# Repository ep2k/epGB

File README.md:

# epGB - Game Boy / Game Boy Color Emulator on an FPGA

epGB is an implementation of Nintendo's __Game Boy__ (__GB__) and __Game Boy Color__ (__GBC__) written in SystemVerilog.
It works on an FPGA board with a board for connection to GB/GBC cartridges.

It has no built-in MBCs, and can basically only operate in real-time communication with cartridges.

The system automatically detects whether the cartridge is "for GB", "GB/GBC dual compatible" or "for GBC only" and starts up in GB mode or GBC mode accordingly.
In the case of a "GB/GBC dual compatible" cartridge, it is also possible to force startup in GB mode.

By using an expansion board equipped with a link port, it is possible to communicate with an actual GB/GBC device via a Nintendo __Game Link Cable__.

The operation has been confirmed with Terasic DE0-CV Board.

---
Demo Video:  
<https://youtu.be/pQHvBj9nH0k>

---

<br>

")

")

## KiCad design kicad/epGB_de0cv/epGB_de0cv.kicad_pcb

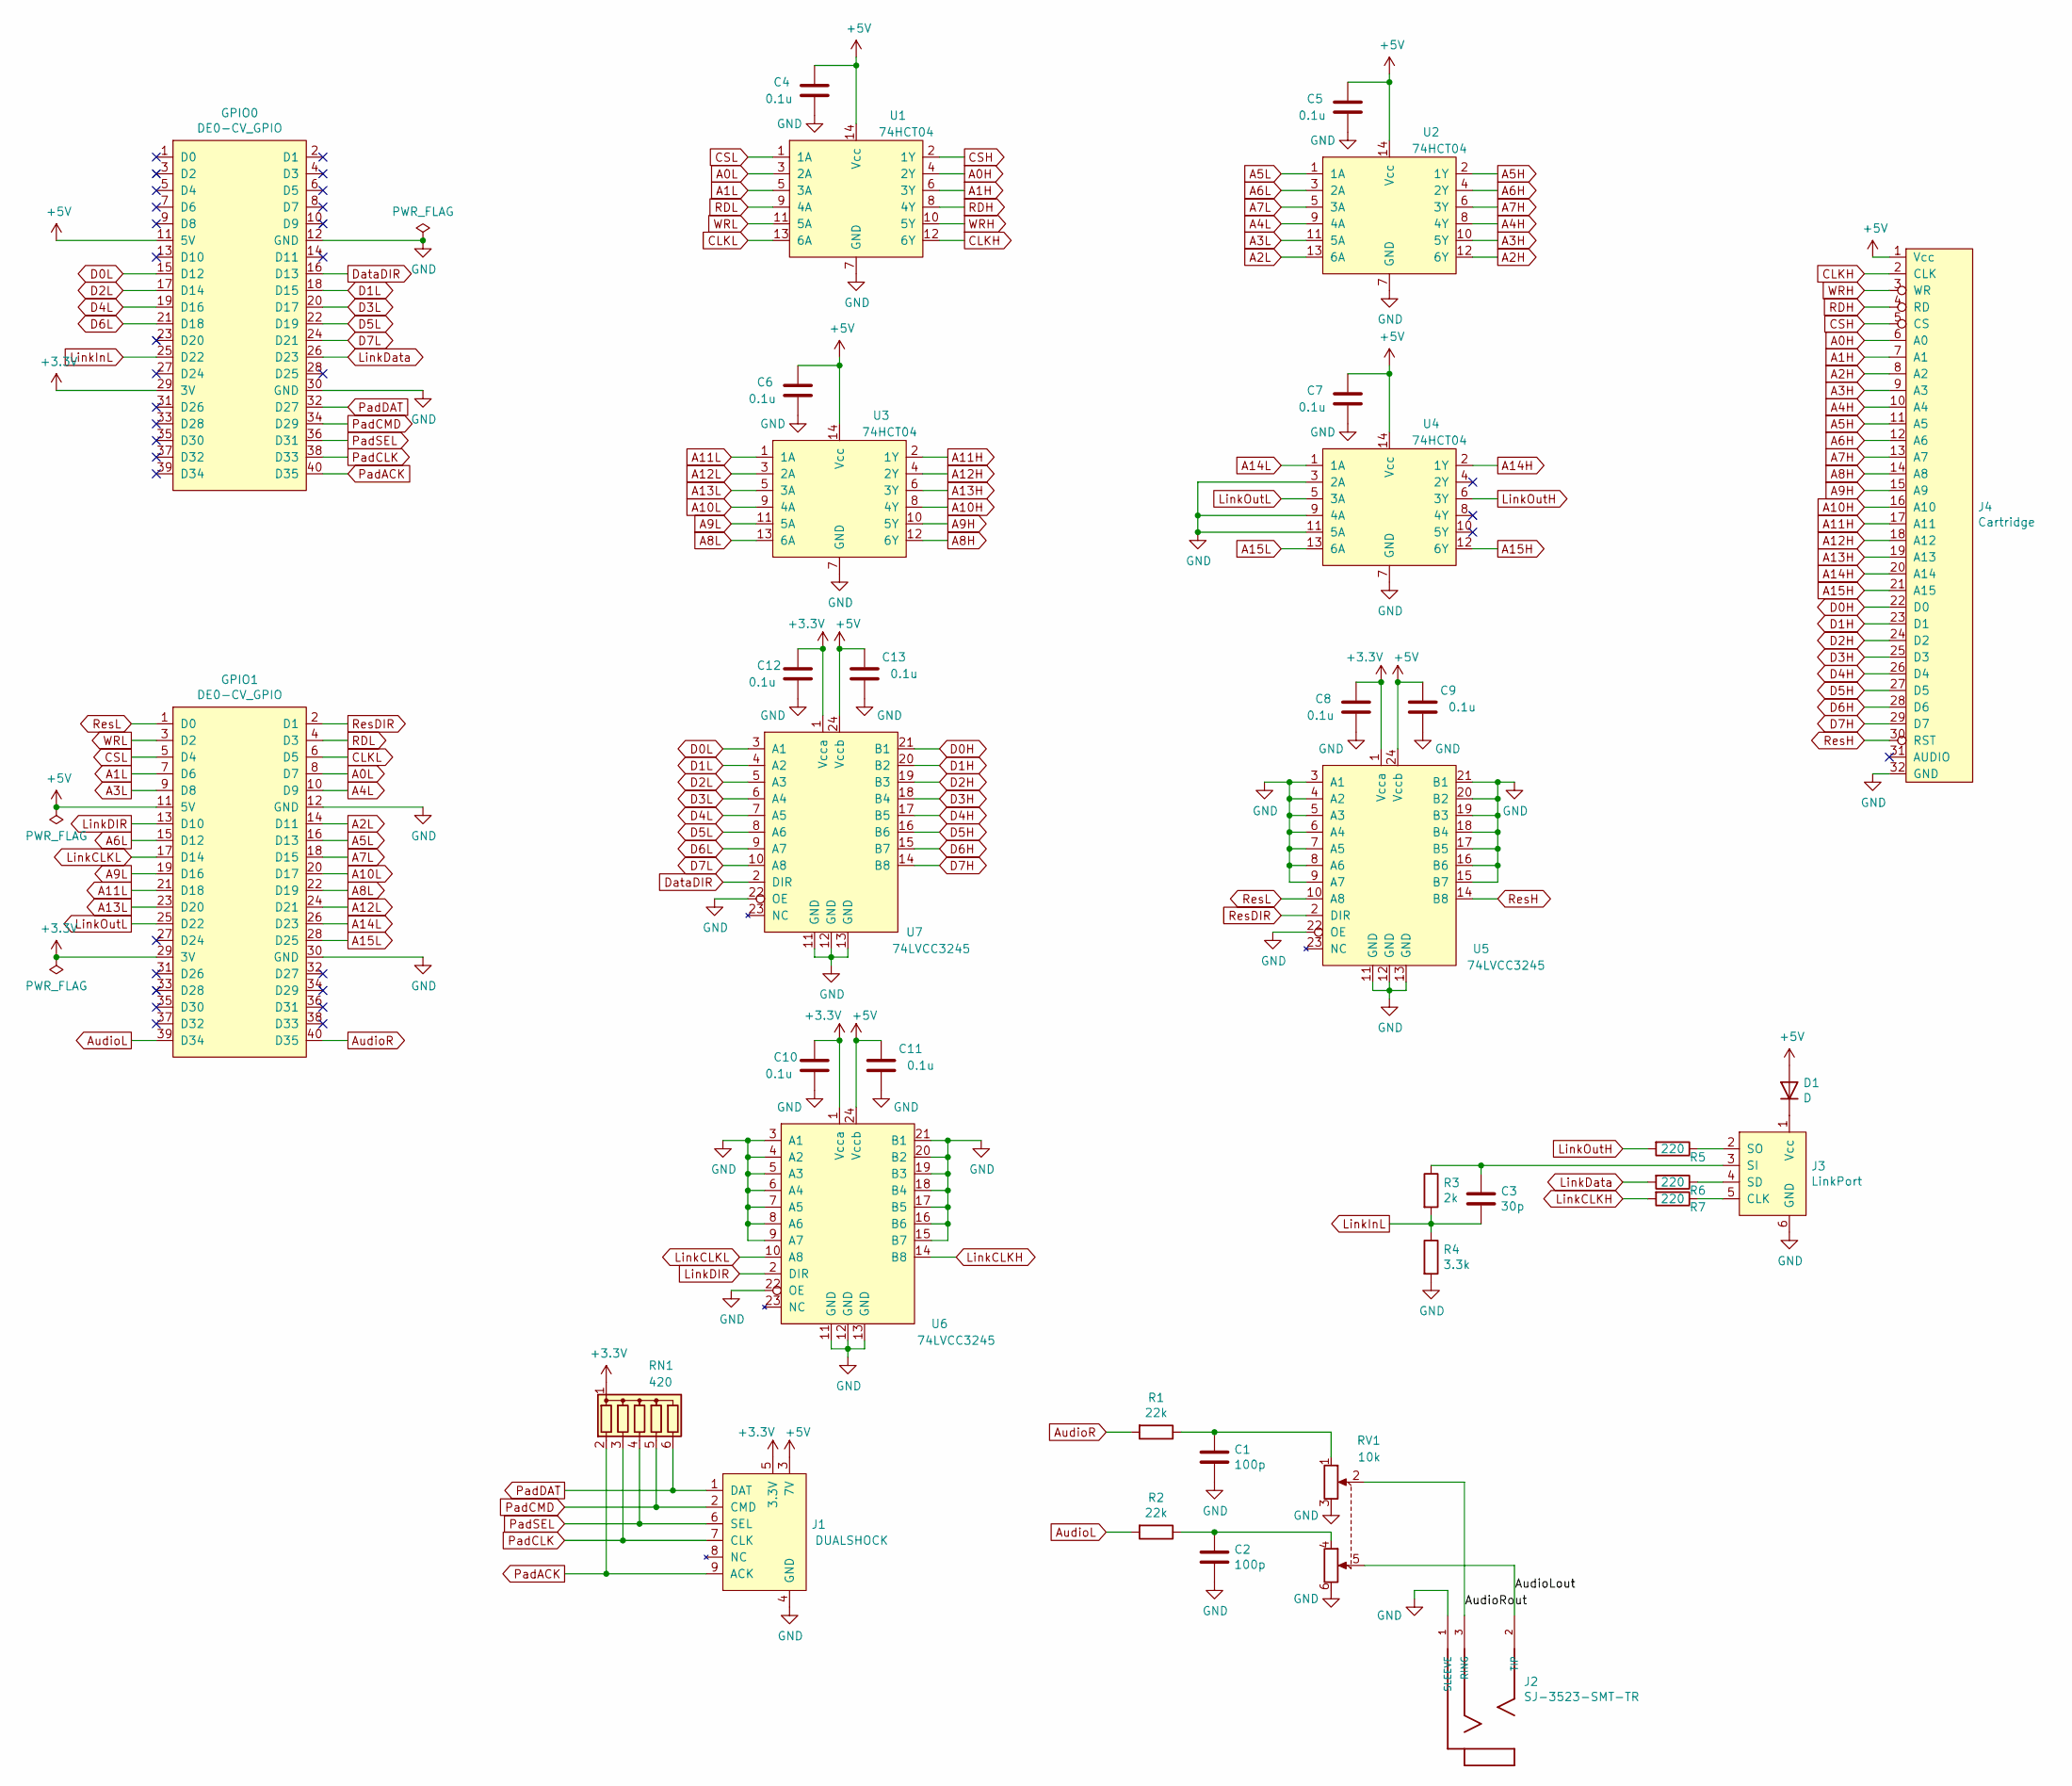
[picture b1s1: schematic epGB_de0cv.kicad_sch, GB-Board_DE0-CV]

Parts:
C1, C2: 100p; C_1206_3216Metric_Pad1.33x1.80mm_HandSolder
C3: 30p; C_1206_3216Metric_Pad1.33x1.80mm_HandSolder
C4, C5, C6, C7, C8, C9, C10, C11, C12, C13: 0.1u; C_1206_3216Metric_Pad1.33x1.80mm_HandSolder
D1: D; D_1206_3216Metric_Pad1.42x1.75mm_HandSolder
GPIO0, GPIO1: DE0-CV_GPIO; PinSocket_2x20_P2.54mm_Vertical_Back
J1: DUALSHOCK; DUALSHOCK_Port
J2: SJ-3523-SMT-TR; CUI_SJ-3523-SMT-TR
J3: LinkPort; Game_Boy_Link_Port
J4: Cartridge; Game_Boy_Card_Edge_Connector
R1, R2: 22k; R_1206_3216Metric_Pad1.30x1.75mm_HandSolder
R3: 2k; R_1206_3216Metric_Pad1.30x1.75mm_HandSolder
R4: 3.3k; R_1206_3216Metric_Pad1.30x1.75mm_HandSolder
R5, R6, R7: 220; R_1206_3216Metric_Pad1.30x1.75mm_HandSolder
RN1: 420; R_Array_SIP6
RV1: 10k; Potentiometer_Bourns_PTV112
U1, U2, U3, U4: 74HCT04; SOIC-14_3.9x8.7mm_P1.27mm
U5, U6, U7: 74LVCC3245; SO-24_5.3x15mm_P1.27mm

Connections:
+3.3V: C8.1, C10.1, C12.1, GPIO0.29 (3V), GPIO1.29 (3V), J1.5 (3.3V), RN1.1 (common), U5.1 (Vcca), U6.1 (Vcca), U7.1 (Vcca)
+5V: C4.1, C5.1, C6.1, C7.1, C9.1, C11.1, C13.1, D1.2 (A), GPIO0.11 (5V), GPIO1.11 (5V), J1.3 (7V), J4.1 (Vcc), U1.14 (Vcc), U2.14 (Vcc), U3.14 (Vcc), U4.14 (Vcc), U5.24 (Vccb), U6.24 (Vccb), U7.24 (Vccb)
/AudioLout: J2.2 (TIP), RV1.5
/AudioRout: J2.3 (RING), RV1.2
A0H: J4.6 (A0), U1.4 (2Y)
A0L: GPIO1.8 (D7), U1.3 (2A)
A1H: J4.7 (A1), U1.6 (3Y)
A1L: GPIO1.7 (D6), U1.5 (3A)
A2H: J4.8 (A2), U2.12 (6Y)
A2L: GPIO1.14 (D11), U2.13 (6A)
A3H: J4.9 (A3), U2.10 (5Y)
A3L: GPIO1.9 (D8), U2.11 (5A)
A4H: J4.10 (A4), U2.8 (4Y)
A4L: GPIO1.10 (D9), U2.9 (4A)
A5H: J4.11 (A5), U2.2 (1Y)
A5L: GPIO1.16 (D13), U2.1 (1A)
A6H: J4.12 (A6), U2.4 (2Y)
A6L: GPIO1.15 (D12), U2.3 (2A)
A7H: J4.13 (A7), U2.6 (3Y)
A7L: GPIO1.18 (D15), U2.5 (3A)
A8H: J4.14 (A8), U3.12 (6Y)
A8L: GPIO1.22 (D19), U3.13 (6A)
A9H: J4.15 (A9), U3.10 (5Y)
A9L: GPIO1.19 (D16), U3.11 (5A)
A10H: J4.16 (A10), U3.8 (4Y)
A10L: GPIO1.20 (D17), U3.9 (4A)
A11H: J4.17 (A11), U3.2 (1Y)
A11L: GPIO1.21 (D18), U3.1 (1A)
A12H: J4.18 (A12), U3.4 (2Y)
A12L: GPIO1.24 (D21), U3.3 (2A)
A13H: J4.19 (A13), U3.6 (3Y)
A13L: GPIO1.23 (D20), U3.5 (3A)
A14H: J4.20 (A14), U4.2 (1Y)
A14L: GPIO1.26 (D23), U4.1 (1A)
A15H: J4.21 (A15), U4.12 (6Y)
A15L: GPIO1.28 (D25), U4.13 (6A)
AudioL: GPIO1.39 (D34), R2.2
AudioR: GPIO1.40 (D35), R1.2
CLKH: J4.2 (CLK), U1.12 (6Y)
CLKL: GPIO1.6 (D5), U1.13 (6A)
CSH: J4.5 (CS), U1.2 (1Y)
CSL: GPIO1.5 (D4), U1.1 (1A)
D0H: J4.22 (D0), U7.21 (B1)
D0L: GPIO0.15 (D12), U7.3 (A1)
D1H: J4.23 (D1), U7.20 (B2)
D1L: GPIO0.18 (D15), U7.4 (A2)
D2H: J4.24 (D2), U7.19 (B3)
D2L: GPIO0.17 (D14), U7.5 (A3)
D3H: J4.25 (D3), U7.18 (B4)
D3L: GPIO0.20 (D17), U7.6 (A4)
D4H: J4.26 (D4), U7.17 (B5)
D4L: GPIO0.19 (D16), U7.7 (A5)
D5H: J4.27 (D5), U7.16 (B6)
D5L: GPIO0.22 (D19), U7.8 (A6)
D6H: J4.28 (D6), U7.15 (B7)
D6L: GPIO0.21 (D18), U7.9 (A7)
D7H: J4.29 (D7), U7.14 (B8)
D7L: GPIO0.24 (D21), U7.10 (A8)
DataDIR: GPIO0.16 (D13), U7.2 (DIR)
GND: C1.2, C2.2, C4.2, C5.2, C6.2, C7.2, C8.2, C9.2, C10.2, C11.2, C12.2, C13.2, GPIO0.12 (GND), GPIO0.30 (GND), GPIO1.12 (GND), GPIO1.30 (GND), J1.4 (GND), J2.1 (SLEEVE), J3.6 (GND), J4.32 (GND), R4.2, RV1.3, RV1.6, U1.7 (GND), U2.7 (GND), U3.7 (GND), U4.3 (2A), U4.7 (GND), U4.9 (4A), U4.11 (5A), U5.3 (A1), U5.4 (A2), U5.5 (A3), U5.6 (A4), U5.7 (A5), U5.8 (A6), U5.9 (A7), U5.11 (GND), U5.12 (GND), U5.13 (GND), U5.15 (B7), U5.16 (B6), U5.17 (B5), U5.18 (B4), U5.19 (B3), U5.20 (B2), U5.21 (B1), U5.22 (OE), U6.3 (A1), U6.4 (A2), U6.5 (A3), U6.6 (A4), U6.7 (A5), U6.8 (A6), U6.9 (A7), U6.11 (GND), U6.12 (GND), U6.13 (GND), U6.15 (B7), U6.16 (B6), U6.17 (B5), U6.18 (B4), U6.19 (B3), U6.20 (B2), U6.21 (B1), U6.22 (OE), U7.11 (GND), U7.12 (GND), U7.13 (GND), U7.22 (OE)
LinkCLKH: R7.2, U6.14 (B8)
LinkCLKL: GPIO1.17 (D14), U6.10 (A8)
LinkDIR: GPIO1.13 (D10), U6.2 (DIR)
LinkData: GPIO0.26 (D23), R6.2
LinkInL: C3.2, GPIO0.25 (D22), R3.2, R4.1
LinkOutH: R5.2, U4.6 (3Y)
LinkOutL: GPIO1.25 (D22), U4.5 (3A)
unnamed: C1.1, R1.1, RV1.1
unnamed: C2.1, R2.1, RV1.4
unnamed: D1.1 (K), J3.1 (Vcc)
unnamed: J3.5 (CLK), R7.1
unnamed: J3.4 (SD), R6.1
unnamed: C3.1, J3.3 (SI), R3.1
unnamed: J3.2 (SO), R5.1
PadACK: GPIO0.40 (D35), J1.9 (ACK), RN1.2 (R1)
PadCLK: GPIO0.38 (D33), J1.7 (CLK), RN1.3 (R2)
PadCMD: GPIO0.34 (D29), J1.2 (CMD), RN1.5 (R4)
PadDAT: GPIO0.32 (D27), J1.1 (DAT), RN1.6 (R5)
PadSEL: GPIO0.36 (D31), J1.6 (SEL), RN1.4 (R3)
RDH: J4.4 (RD), U1.8 (4Y)
RDL: GPIO1.4 (D3), U1.9 (4A)
ResDIR: GPIO1.2 (D1), U5.2 (DIR)
ResH: J4.30 (RST), U5.14 (B8)
ResL: GPIO1.1 (D0), U5.10 (A8)
WRH: J4.3 (WR), U1.10 (5Y)
WRL: GPIO1.3 (D2), U1.11 (5A)

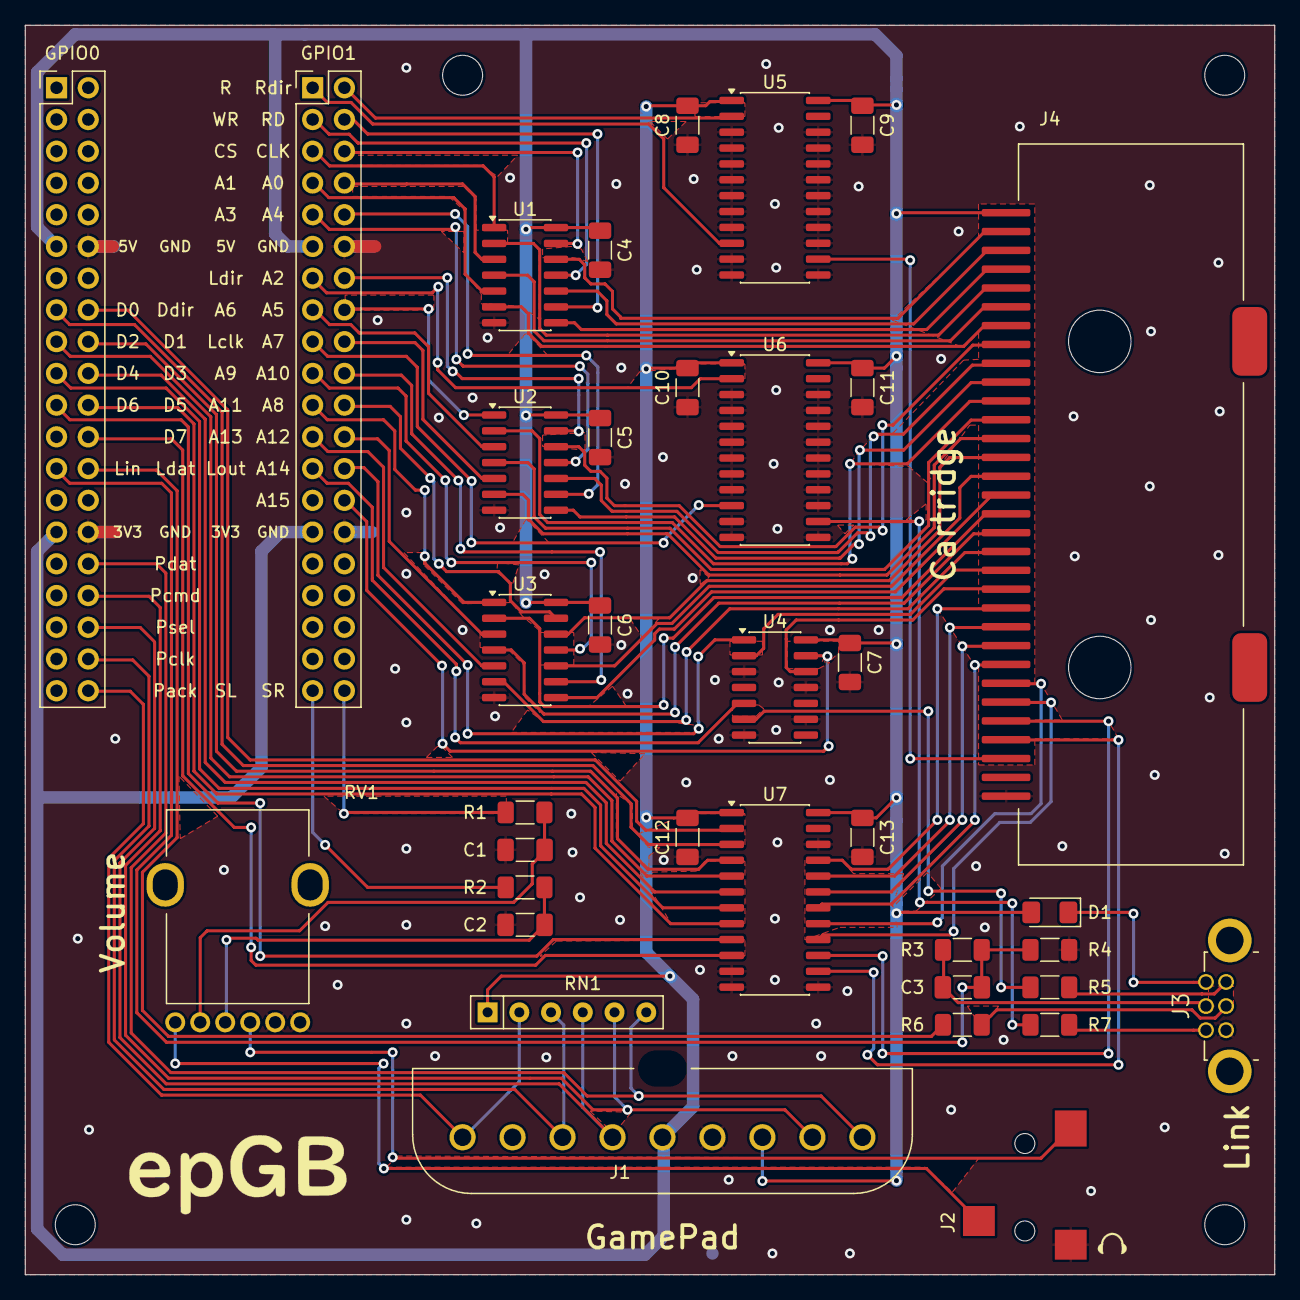
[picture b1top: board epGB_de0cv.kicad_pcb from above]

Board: 2 copper layers, 100.0 x 100.0 mm, 36 parts (0 on the bottom side), 86 nets.

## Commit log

2023-03-12 Create LICENSE
2024-01-10 Add pcb.png
2025-11-02 feat: #3 .gitignoreを追加
2025-11-02 feat: #3 カートリッジ接続基板のKiCadデータを追加
